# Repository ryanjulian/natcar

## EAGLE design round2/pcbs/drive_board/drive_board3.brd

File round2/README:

This is the Git tree for group 10 in EE192 Spring 2012 at UC Berkeley.

It contains LabVIEW diagrams, C source code, and PCB designs for a robotic car designed to compete in the annual NatCar competition.

For more information on EE192 and NatCar, see http://inst.eecs.berkeley.edu/~ee192/sp12/index.html and http://www.ece.ucdavis.edu/natcar/.

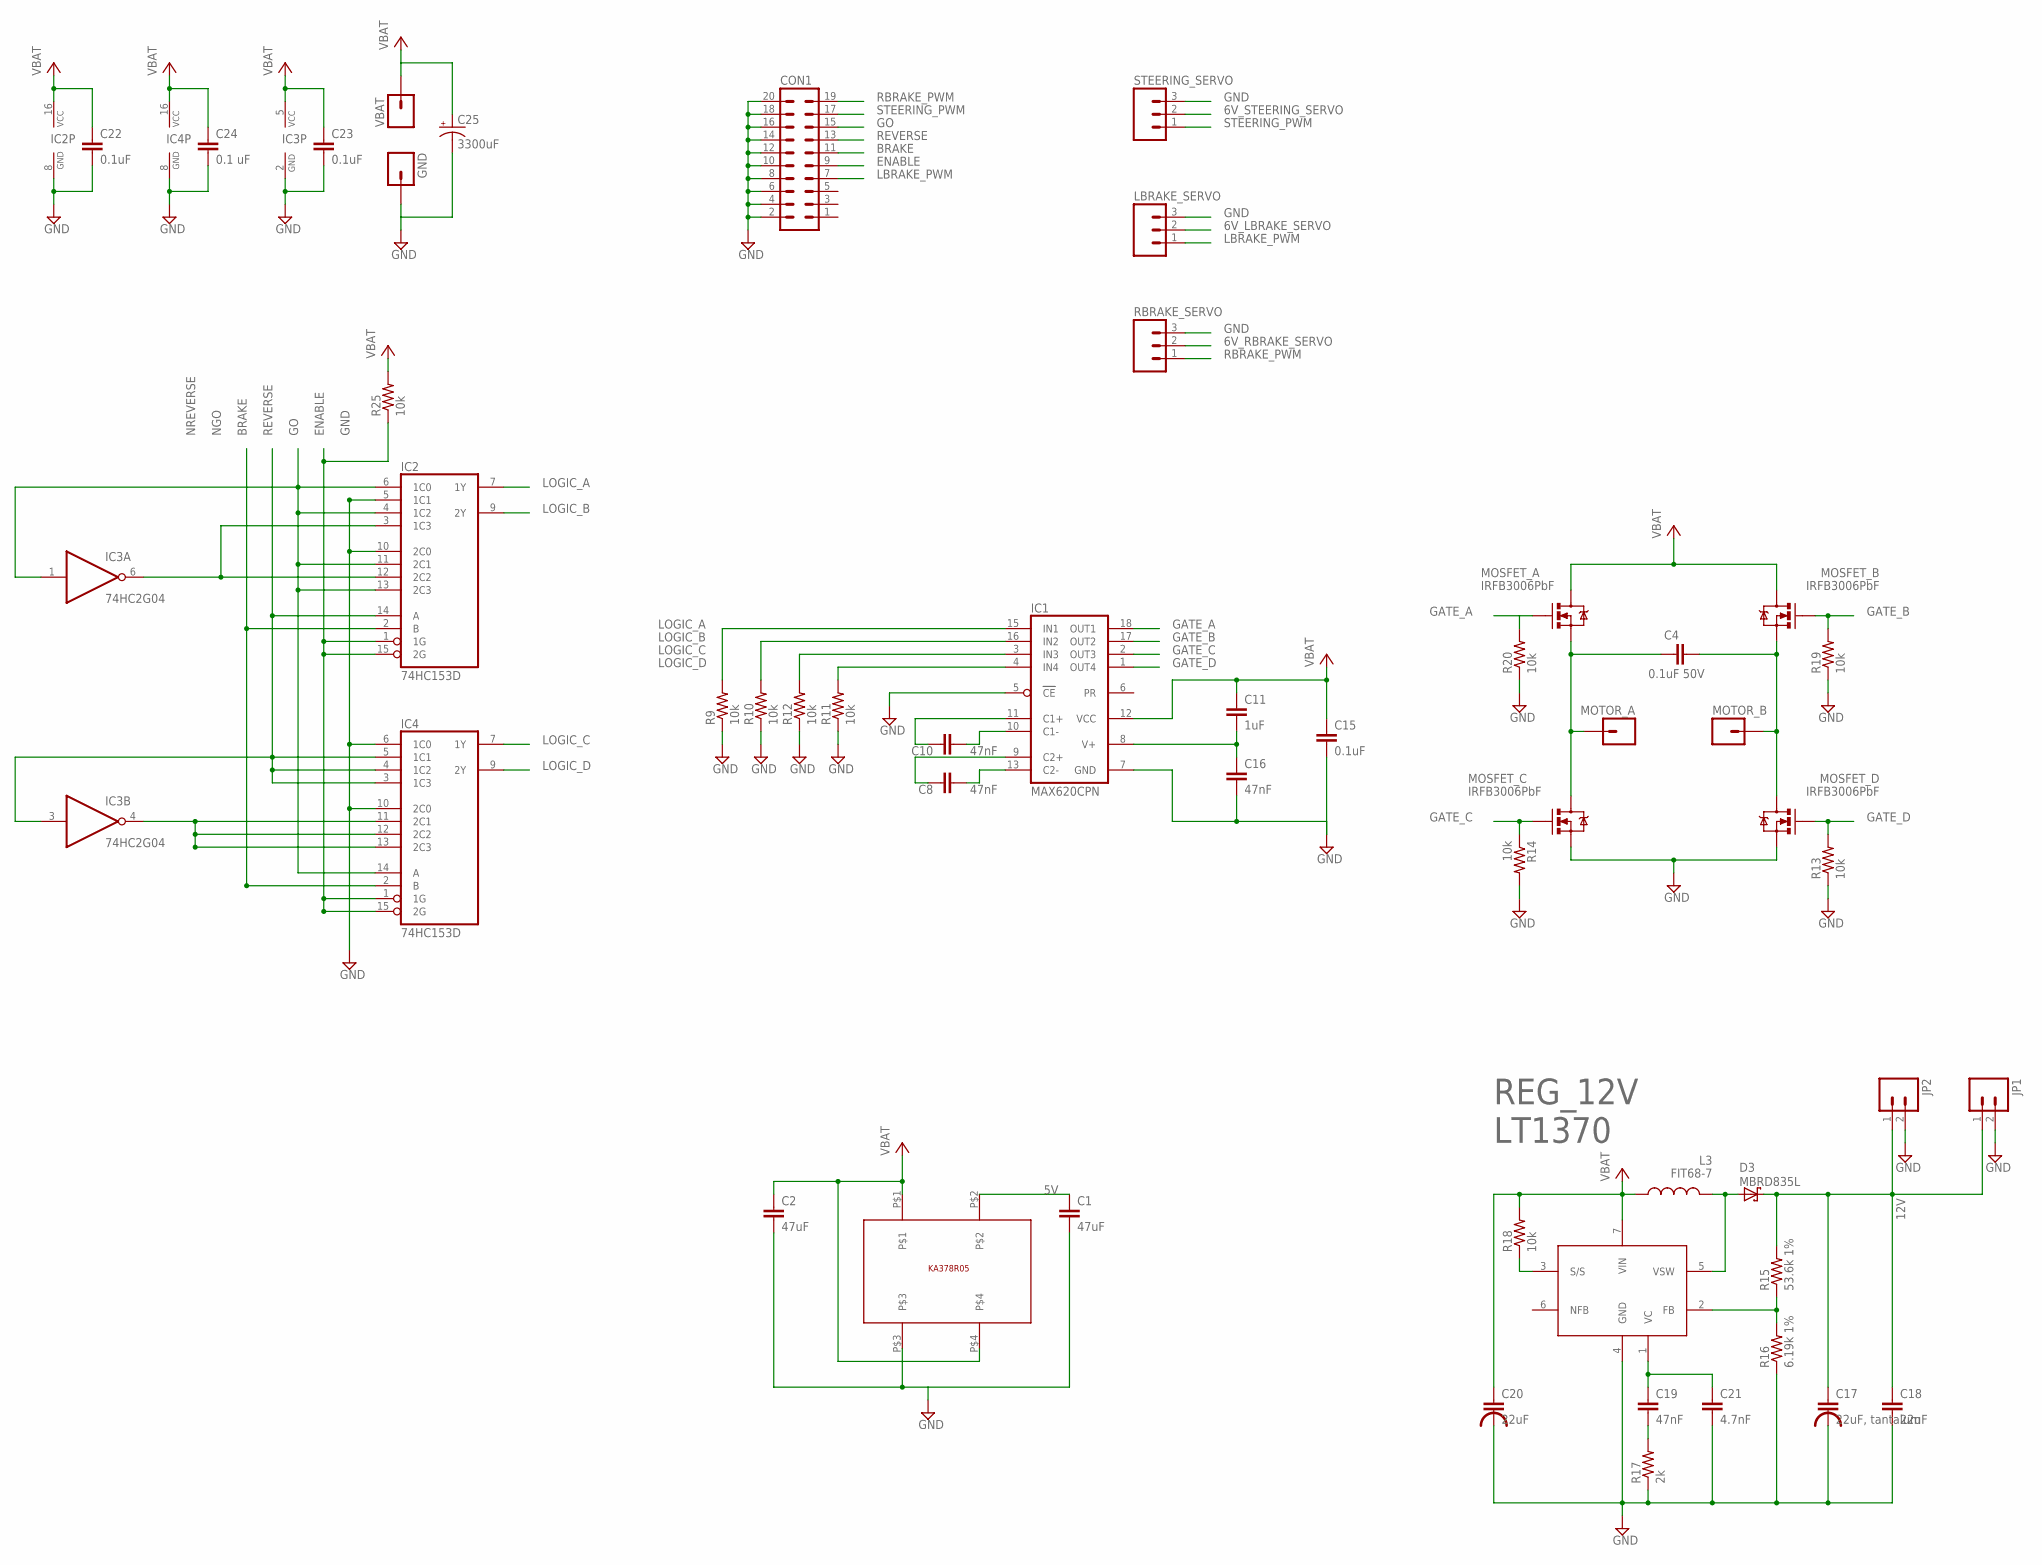
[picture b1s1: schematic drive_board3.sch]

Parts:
C1, C2: 47uF; 0603-CAP
C4: 0.1uF 50V; 0603-CAP
C8, C10, C16, C19: 47nF; 0603-CAP
C11: 1uF; 0603-CAP
C15, C22, C23: 0.1uF; 0603-CAP
C17: 22uF, tantalum; CAPACITOR_CASE_D
C18: 22uF; 0603-CAP
C20: 22uF; CAPACITOR_CASE_D
C21: 4.7nF; 0603-CAP
C24: 0.1 uF; 0603-CAP
C25: 3300uF; CPOL-RADIAL-100UF-25V
CON1: ML20
D3: MBRD835L; DPACK_1
GND: GND; PAD_12GA
IC1: MAX620CPN; DIL18
IC2, IC4: 74HC153D; SO16
IC3: 74HC2G04; TSSOP6
JP1, JP2: M025MM; SCREWTERMINAL-5MM-2
L3: FIT68-7; TOROID_INDUCTOR
LBRAKE_SERVO: M03POLAR; MOLEX-1X3
MOSFET_A: IRFB3006PbF; TO220V
MOSFET_B: IRFB3006PbF; TO220V
MOSFET_C: IRFB3006PbF; TO220V
MOSFET_D: IRFB3006PbF; TO220V
MOTOR_A: MOTOR A; PAD_12GA
MOTOR_B: MOTOR B; PAD_12GA
R9, R10, R11, R12, R13, R14, R18, R19, R20, R25: 10k; 0603-RES
R15: 53.6k 1%; 0603-RES
R16: 6.19k 1%; 0603-RES
R17: 2k; 0603-RES
RBRAKE_SERVO: M03POLAR; MOLEX-1X3
REG_12V: LT1370; TO220-7
STEERING_SERVO: M03POLAR; MOLEX-1X3
U$5: KA378R05; TO-220-4L
VBAT: 7.2V; PAD_12GA

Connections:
6V_LBRAKE_SERVO: LBRAKE_SERVO.2
6V_RBRAKE_SERVO: RBRAKE_SERVO.2
6V_STEERING_SERVO: STEERING_SERVO.2
12V: C17.P$1 (1), C18.1, D3.C, JP1.1, JP2.1, R15.2
BRAKE: CON1.11, IC2.2 (B), IC4.2 (B)
ENABLE: CON1.9, IC2.1 (1G), IC2.15 (2G), IC4.1 (1G), IC4.15 (2G), R25.1
GATE_A: IC1.18 (OUT1), MOSFET_A.1 (G), R20.2
GATE_B: IC1.17 (OUT2), MOSFET_B.1 (G), R19.2
GATE_C: IC1.2 (OUT3), MOSFET_C.1 (G), R14.1
GATE_D: IC1.1 (OUT4), MOSFET_D.1 (G), R13.2
GND: C1.2, C2.2, C15.2, C16.2, C17.P$2 (2), C18.2, C20.P$2 (2), C21.2, C22.2, C23.2, C24.2, C25.2 (-), CON1.2, CON1.4, CON1.6, CON1.8, CON1.10, CON1.12, CON1.14, CON1.16, CON1.18, CON1.20, GND.1, IC1.5 (CE), IC1.7 (GND), IC2.5 (1C1), IC2.8 (GND), IC2.10 (2C0), IC3.2 (GND), IC4.6 (1C0), IC4.8 (GND), IC4.10 (2C0), JP1.2, JP2.2, LBRAKE_SERVO.3, MOSFET_C.3 (S), MOSFET_D.3 (S), R9.1, R10.1, R11.1, R12.1, R13.1, R14.2, R16.1, R17.1, R19.1, R20.1, RBRAKE_SERVO.3, REG_12V.4 (GND), STEERING_SERVO.3, U$5.P$3
GO: CON1.15, IC2.4 (1C2), IC2.6 (1C0), IC2.11 (2C1), IC2.13 (2C3), IC3.1 (I), IC4.14 (A)
LBRAKE_PWM: CON1.7, LBRAKE_SERVO.1
LOGIC_A: IC1.15 (IN1), IC2.7 (1Y), R9.2
LOGIC_B: IC1.16 (IN2), IC2.9 (2Y), R10.2
LOGIC_C: IC1.3 (IN3), IC4.7 (1Y), R12.2
LOGIC_D: IC1.4 (IN4), IC4.9 (2Y), R11.2
MOTOR_A: C4.1, MOSFET_A.3 (S), MOSFET_C.2 (D), MOTOR_A.1
MOTOR_B: C4.2, MOSFET_B.3 (S), MOSFET_D.2 (D), MOTOR_B.1
unnamed: C10.1, IC1.11 (C1+)
unnamed: C10.2, IC1.10 (C1-)
unnamed: C8.2, IC1.13 (C2-)
unnamed: C8.1, IC1.9 (C2+)
unnamed: C1.1, U$5.P$2
unnamed: D3.B (A), D3.E (A), L3.2, REG_12V.5 (VSW)
unnamed: R15.1, R16.2, REG_12V.2 (FB)
unnamed: C19.1, C21.1, REG_12V.1 (VC)
unnamed: C19.2, R17.2
unnamed: R18.1, REG_12V.3 (S/S)
NGO: IC2.3 (1C3), IC2.12 (2C2), IC3.6 (O)
NREVERSE: IC3.4 (O), IC4.11 (2C1), IC4.12 (2C2), IC4.13 (2C3)
RBRAKE_PWM: CON1.19, RBRAKE_SERVO.1
REVERSE: CON1.13, IC2.14 (A), IC3.3 (I), IC4.3 (1C3), IC4.4 (1C2), IC4.5 (1C1)
STEERING_PWM: CON1.17, STEERING_SERVO.1
V+: C11.2, C16.1, IC1.8 (V+)
VBAT: C11.1, C15.1, C20.P$1 (1), C22.1, C23.1, C24.1, C25.1 (+), IC1.12 (VCC), IC2.16 (VCC), IC3.5 (VCC), IC4.16 (VCC), L3.1, MOSFET_A.2 (D), MOSFET_B.2 (D), R18.2, REG_12V.7 (VIN), VBAT.1
VCC: C2.1, R25.2, U$5.P$1, U$5.P$4

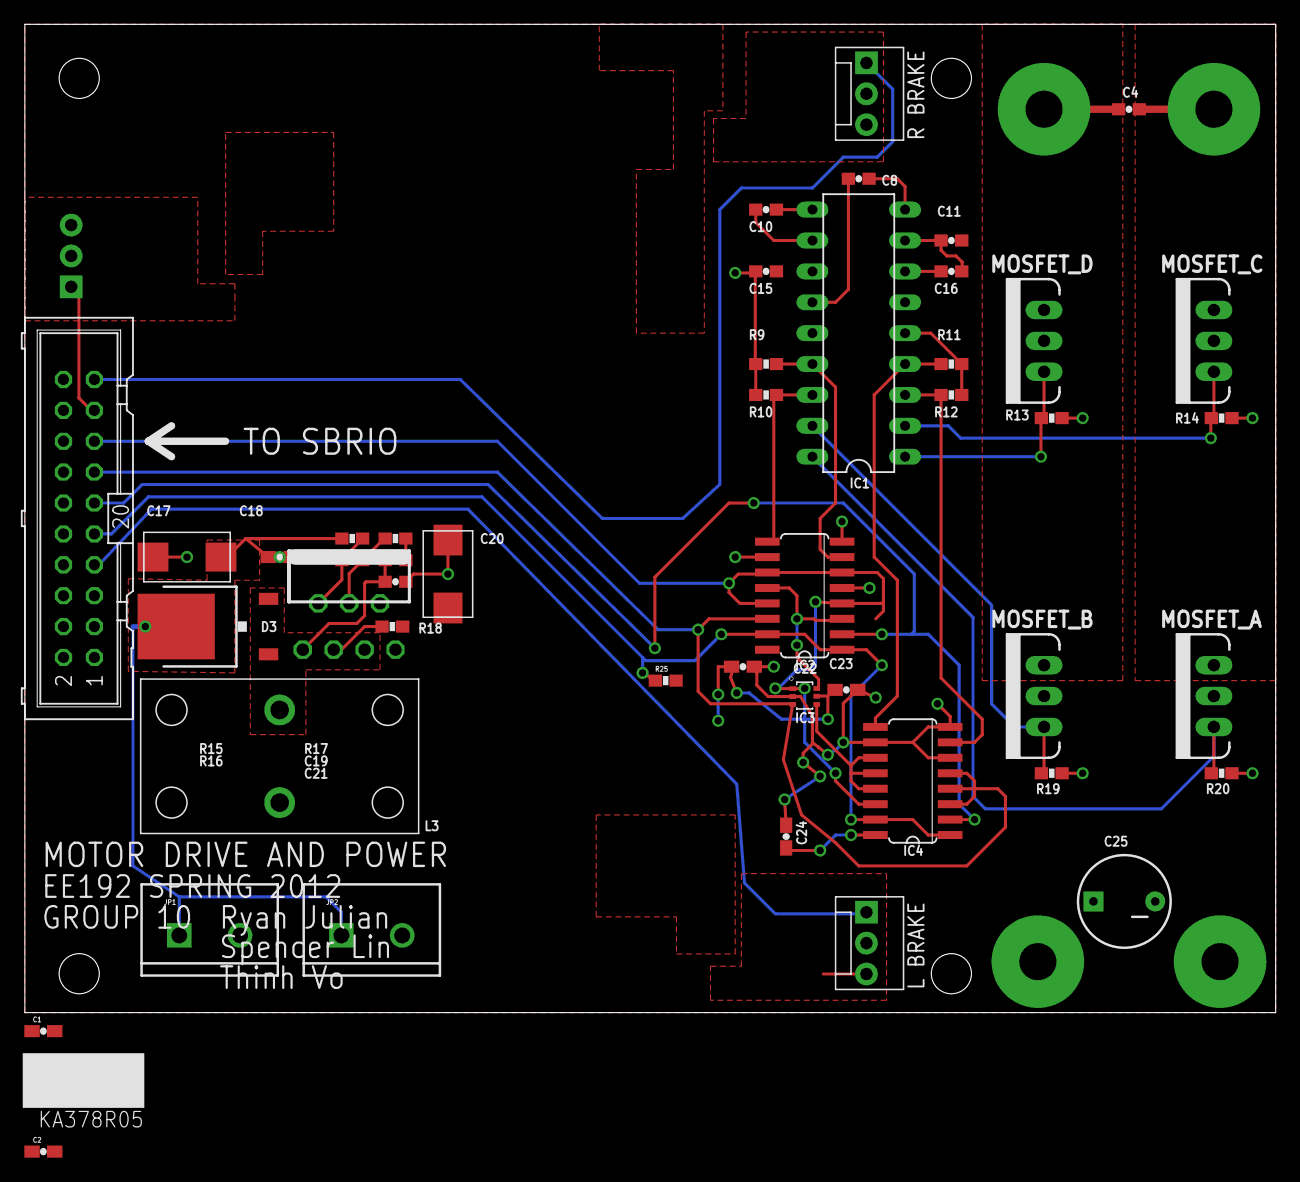
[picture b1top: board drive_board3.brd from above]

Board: 2 copper layers, 102.9 x 81.3 mm, 56 parts (1 on the bottom side), 34 nets.

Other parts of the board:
U$1, U$2, U$3, U$4: STAND-OFF

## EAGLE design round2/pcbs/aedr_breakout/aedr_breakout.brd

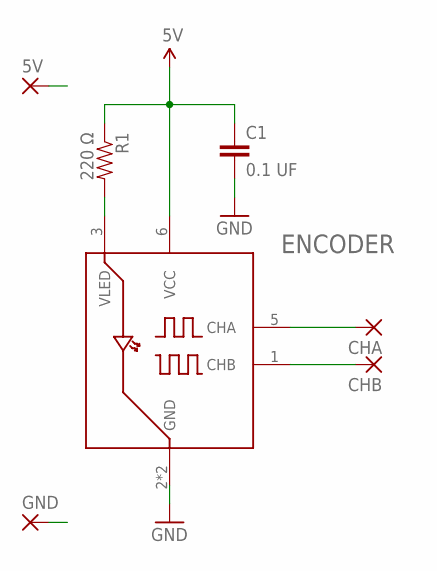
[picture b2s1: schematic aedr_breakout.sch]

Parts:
5V: WIREPADSMD1,27-254; SMD1,27-2,54
C1: 0.1 UF; 0402-CAP
CHA: WIREPADSMD1,27-254; SMD1,27-2,54
CHB: WIREPADSMD1,27-254; SMD1,27-2,54
ENCODER: AEDR-8300-K; AEDR-8300
GND: WIREPADSMD1,27-254; SMD1,27-2,54
R1: 220 Ω; 0402-RES

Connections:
5V: 5V.1, C1.1, ENCODER.6 (VCC), R1.1
CHA: CHA.1, ENCODER.5 (CHA)
CHB: CHB.1, ENCODER.1 (CHB)
GND: C1.2, ENCODER.2 (GND), ENCODER.4 (GND)
unnamed: ENCODER.3 (VLED), R1.2

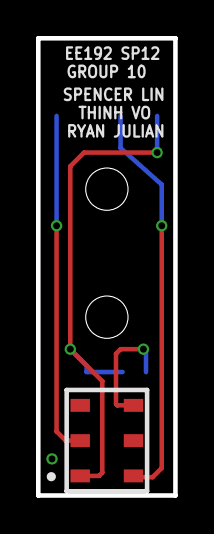
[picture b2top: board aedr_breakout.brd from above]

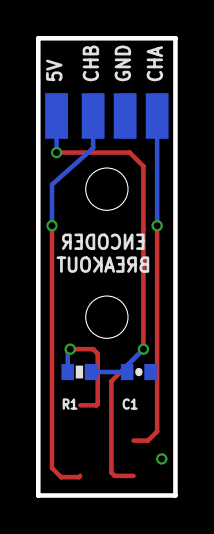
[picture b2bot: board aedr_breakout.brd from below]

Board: 2 copper layers, 7.6 x 25.4 mm, 9 parts (6 on the bottom side), 5 nets.

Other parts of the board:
U$1, U$4: HOLE-2-56

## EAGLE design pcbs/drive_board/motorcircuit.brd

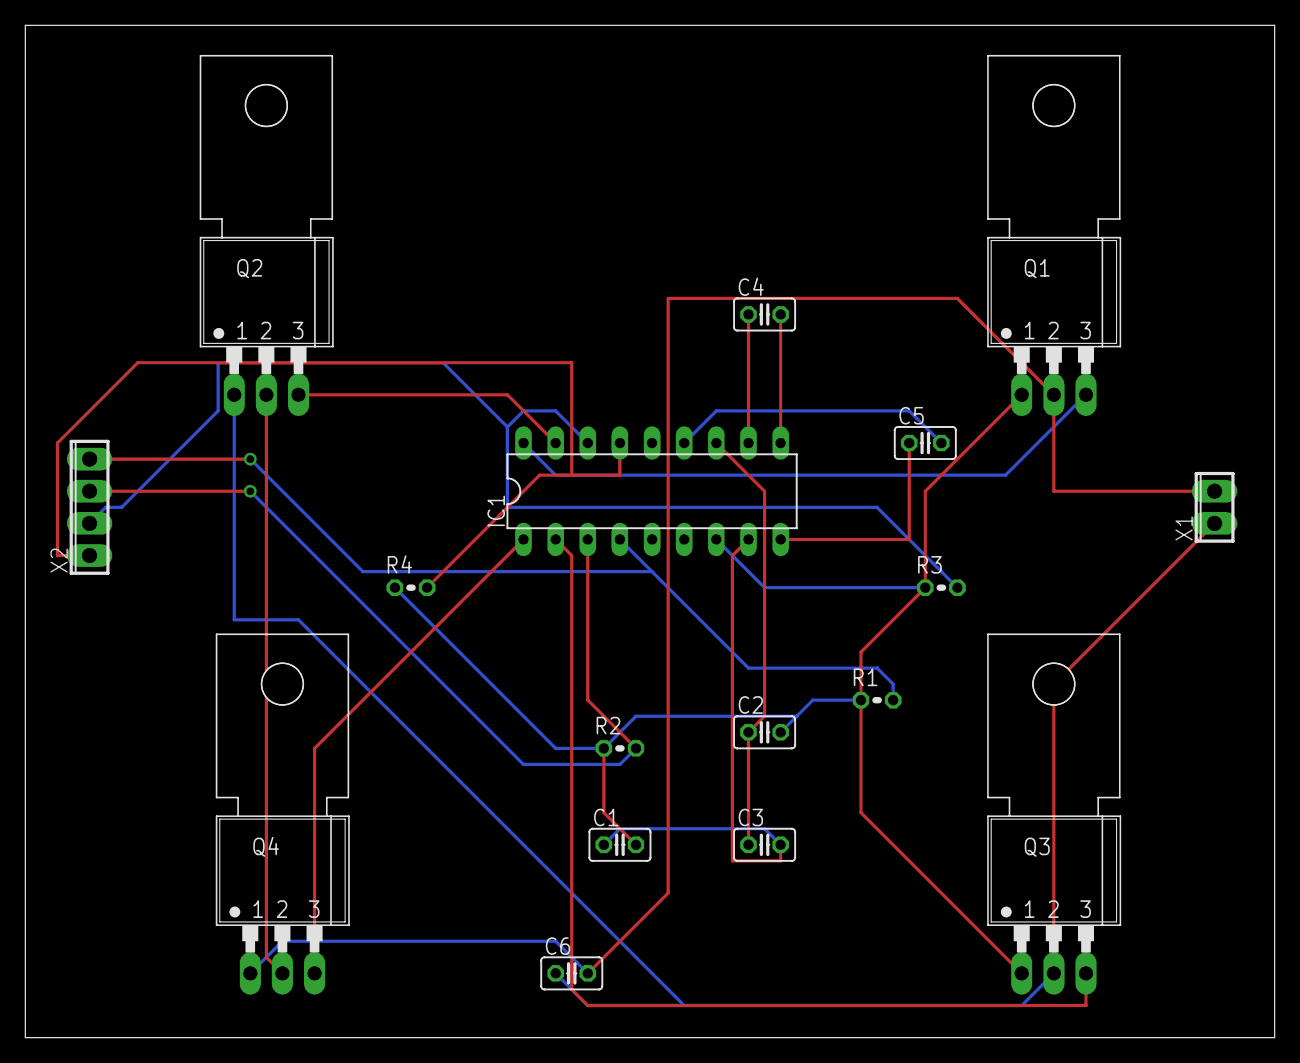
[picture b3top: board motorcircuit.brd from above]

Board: 2 copper layers, 98.7 x 80.0 mm, 17 parts (0 on the bottom side), 18 nets.

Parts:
C1, C2, C3, C4, C5, C6: C025-025X050
IC1: MAX620CPN; DIL18
Q1, Q2, Q3, Q4: BSS97; TO202
R1, R2, R3, R4: 0204V
X1: 2POL254
X2: 4POL254

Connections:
+7V: Q2.2, Q4.2
GND: C1.2, C2.2, IC1.7, Q1.1, Q3.1, R1.1, R2.1, R3.1, R4.1
unnamed: IC1.18, Q1.3
unnamed: IC1.17, Q2.3
unnamed: IC1.2, Q3.3
unnamed: IC1.1, Q4.3
unnamed: IC1.3, R2.2, X2.3
unnamed: IC1.4, R1.2, X2.4
unnamed: C4.2, IC1.10
unnamed: C4.1, IC1.11
unnamed: C5.1, IC1.9
unnamed: C5.2, IC1.13
unnamed: IC1.16, R3.2, X2.2
unnamed: IC1.15, R4.2, X2.1
unnamed: C6.1, Q2.1, Q3.2, X1.1
unnamed: C6.2, Q1.2, Q4.1, X1.2
V+: C1.1, C3.2, IC1.8
VCC: C2.1, C3.1, IC1.12

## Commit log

2012-02-29 Initial add
2012-02-29 Add README
2012-03-01 Fixed Microblaze clock issue found by Trung. JTAG still not working.
2012-03-01 MicroBlaze hello world working (thanks to Trung!)
2012-03-02 my first commit has lots of awesome changes
2012-03-02 New 40MHz uBlaze
2012-03-02 hooked up labview
2012-03-08 driveboard v2 complete
2012-03-09 XPS/uBlaze: Added LVFPGA MMIO interface
    LVFPGA:
    Added SPI ADC IP and LVFPGA MMIO interface
2012-03-09 Non-working ADC + Host interface
2012-03-09 ADC/Host Interface now compiles.
2012-03-09 Add new files from ADC/Host interface.
2012-03-09 Fully tested and workind ADC/Host Interface
2012-03-16 New uBlaze with triple GPIO
2012-03-16 New SDK project with GPIO input example.
2012-03-20 reorganizing
2012-03-20 push to master checkpoint 8
2012-03-20 cleaned up code (should still be same as working checkpoint 8). not sure if tentative_steering_input should be u16 or double.
2012-04-05 op-amp diagram
2012-04-05 Merging...
2012-04-06 Latest labview
2012-04-06 Remove PCB temp files
2012-04-06 More merging noise
2012-04-06 More clean-up
2012-04-06 Commit before adding new servo code.
2012-04-06 Added precise steering control.
2012-04-06 Checkoff 10
2012-04-08 matlab testing
2012-04-09 pulled ryans stuff
2012-04-09 commiting ryans pull again
2012-04-09 New microblaze with much more GPIO, velocity counts sent to microblaze, interrupt controller
2012-04-09 Added hardware to SDK export
2012-04-09 modified the labview RT file
2012-04-18 working on round 2 labview stuff
2012-04-18 ready for testing and calibrating sensors
2012-04-18 added distance to the data that is recorded (forgot to do it before)
2012-04-18 small changes. everything's good to go except the Analog Inputs need to be mapped to the Sensors.
2012-04-20 added the variables needed to save data on my local machine, and ordered the analog inputs to reflect the sensor setup.
2012-04-20 ryan changed stuff
2012-04-23 working steering
2012-04-23 cleaned up some stuff

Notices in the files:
parts and their libraries:
SparkFun-Passives: Licensing: CC v3.0 Share-Alike You are welcome to use this library for commercial purposes.
SparkFun-Aesthetics: Released under the Creative Commons
SparkFun-Aesthetics: http://creativecommons.org/licenses/by-sa/3.0
